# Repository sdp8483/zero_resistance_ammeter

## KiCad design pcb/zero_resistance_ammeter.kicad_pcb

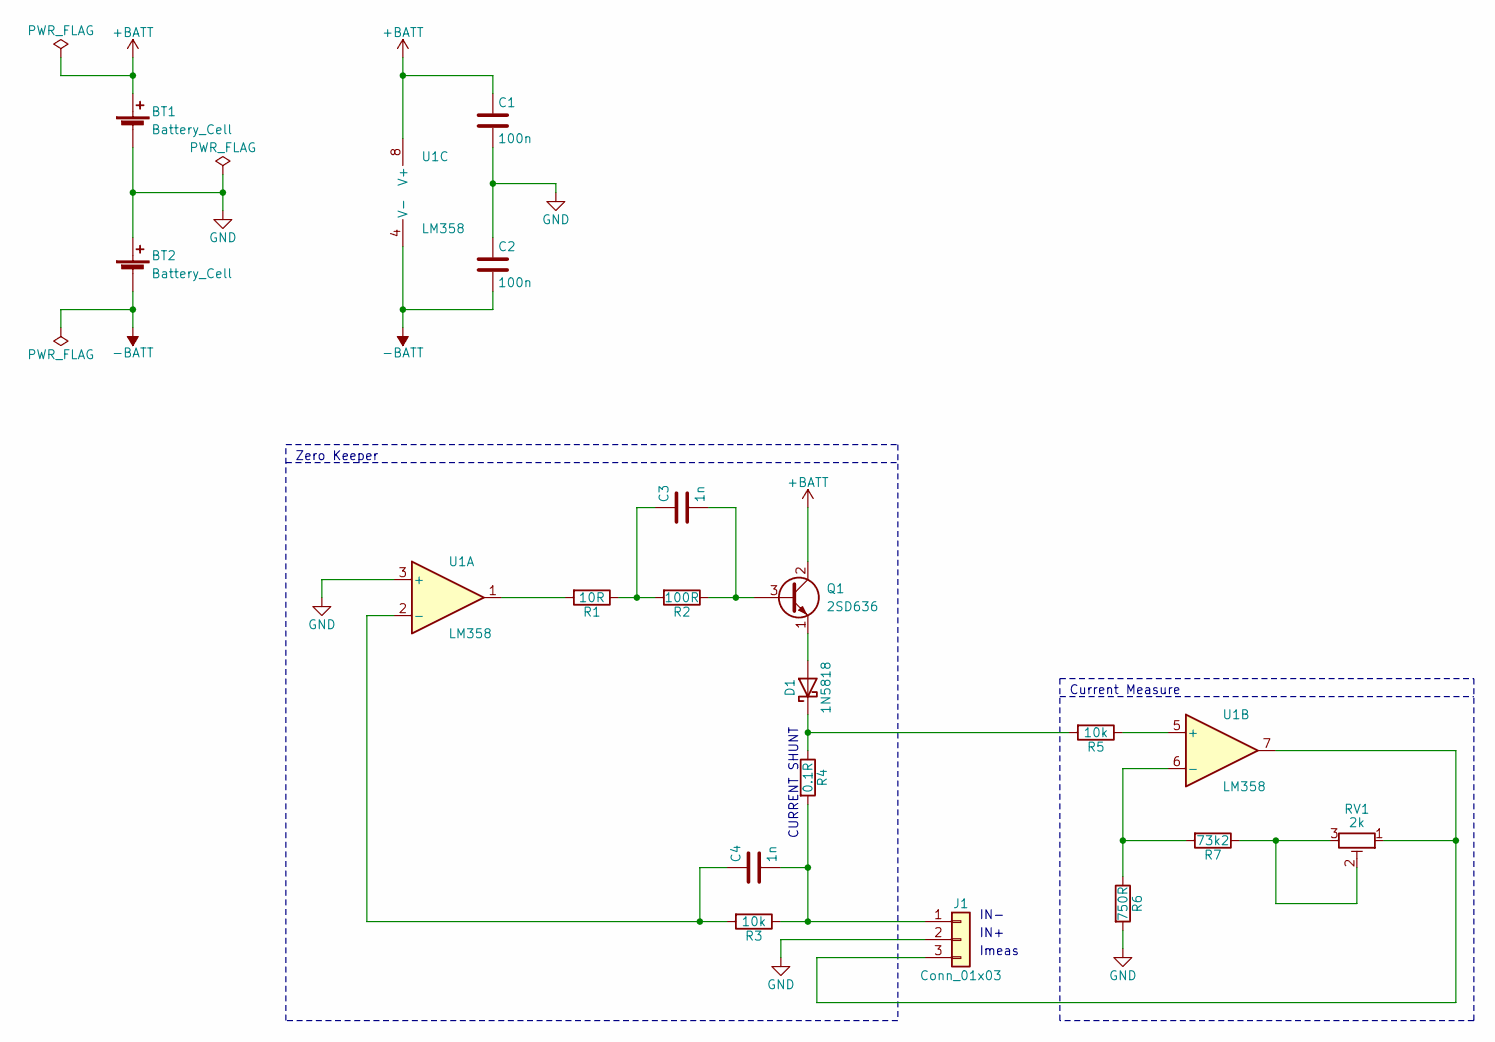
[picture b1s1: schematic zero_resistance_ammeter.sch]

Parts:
BT1, BT2: Battery_Cell; PinHeader_1x02_P2.54mm_Vertical
C1, C2: 100n; C_Rect_L7.0mm_W2.5mm_P5.00mm
C3, C4: 1n; C_Rect_L7.0mm_W2.5mm_P5.00mm
D1: 1N5818; D_DO-15_P10.16mm_Horizontal
J1: Conn_01x03; TerminalBlock_bornier-3_P5.08mm
Q1: 2SD636; PinHeader_1x03_P2.54mm_Vertical
R1: 10R; R_Axial_DIN0207_L6.3mm_D2.5mm_P10.16mm_Horizontal
R2: 100R; R_Axial_DIN0207_L6.3mm_D2.5mm_P10.16mm_Horizontal
R3, R5: 10k; R_Axial_DIN0207_L6.3mm_D2.5mm_P10.16mm_Horizontal
R4: 0.1R; R_2512
R6: 750R; R_Axial_DIN0207_L6.3mm_D2.5mm_P10.16mm_Horizontal
R7: 73k2; R_Axial_DIN0207_L6.3mm_D2.5mm_P10.16mm_Horizontal
RV1: 2k; Potentiometer_Bourns_3005_Horizontal
U1: LM358; DIP-8_W7.62mm

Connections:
+BATT: BT1.1 (+), C1.1, Q1.2 (C), U1.8 (V+)
-BATT: BT2.2 (-), C2.2, U1.4 (V-)
GND: BT1.2 (-), BT2.1 (+), C1.2, C2.1, J1.2, R6.2, U1.3 (+)
unnamed: C3.1, R1.1, R2.2
unnamed: C3.2, Q1.3 (B), R2.1
unnamed: C4.1, R3.2, U1.2 (-)
unnamed: C4.2, J1.1, R3.1, R4.2
unnamed: D1.1 (K), R4.1, R5.2
unnamed: D1.2 (A), Q1.1 (E)
unnamed: J1.3, RV1.1, U1.7
unnamed: R1.2, U1.1
unnamed: R5.1, U1.5 (+)
unnamed: R6.1, R7.2, U1.6 (-)
unnamed: R7.1, RV1.2, RV1.3

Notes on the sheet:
IN-
IN+
Imeas
CURRENT SHUNT
Current Measure
Zero Keeper

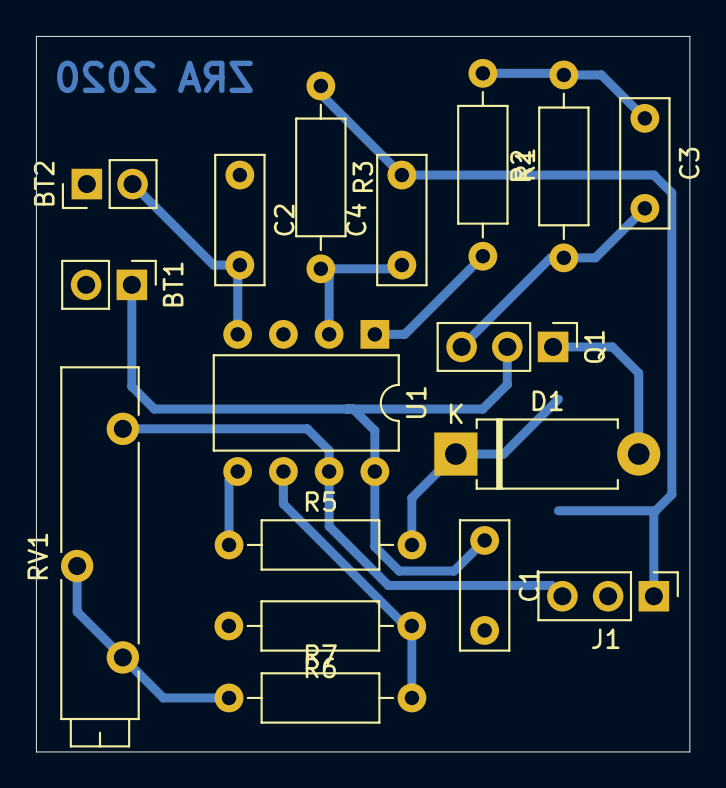
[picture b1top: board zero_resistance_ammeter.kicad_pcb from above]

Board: 2 copper layers, 36.3 x 39.8 mm, 18 parts (1 on the bottom side), 14 nets.

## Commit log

2020-10-28 init commit
2020-10-29 associate footprints
2020-10-29 PCB layout
2020-10-30 plot gerber and drill
2020-10-30 create cnc job
